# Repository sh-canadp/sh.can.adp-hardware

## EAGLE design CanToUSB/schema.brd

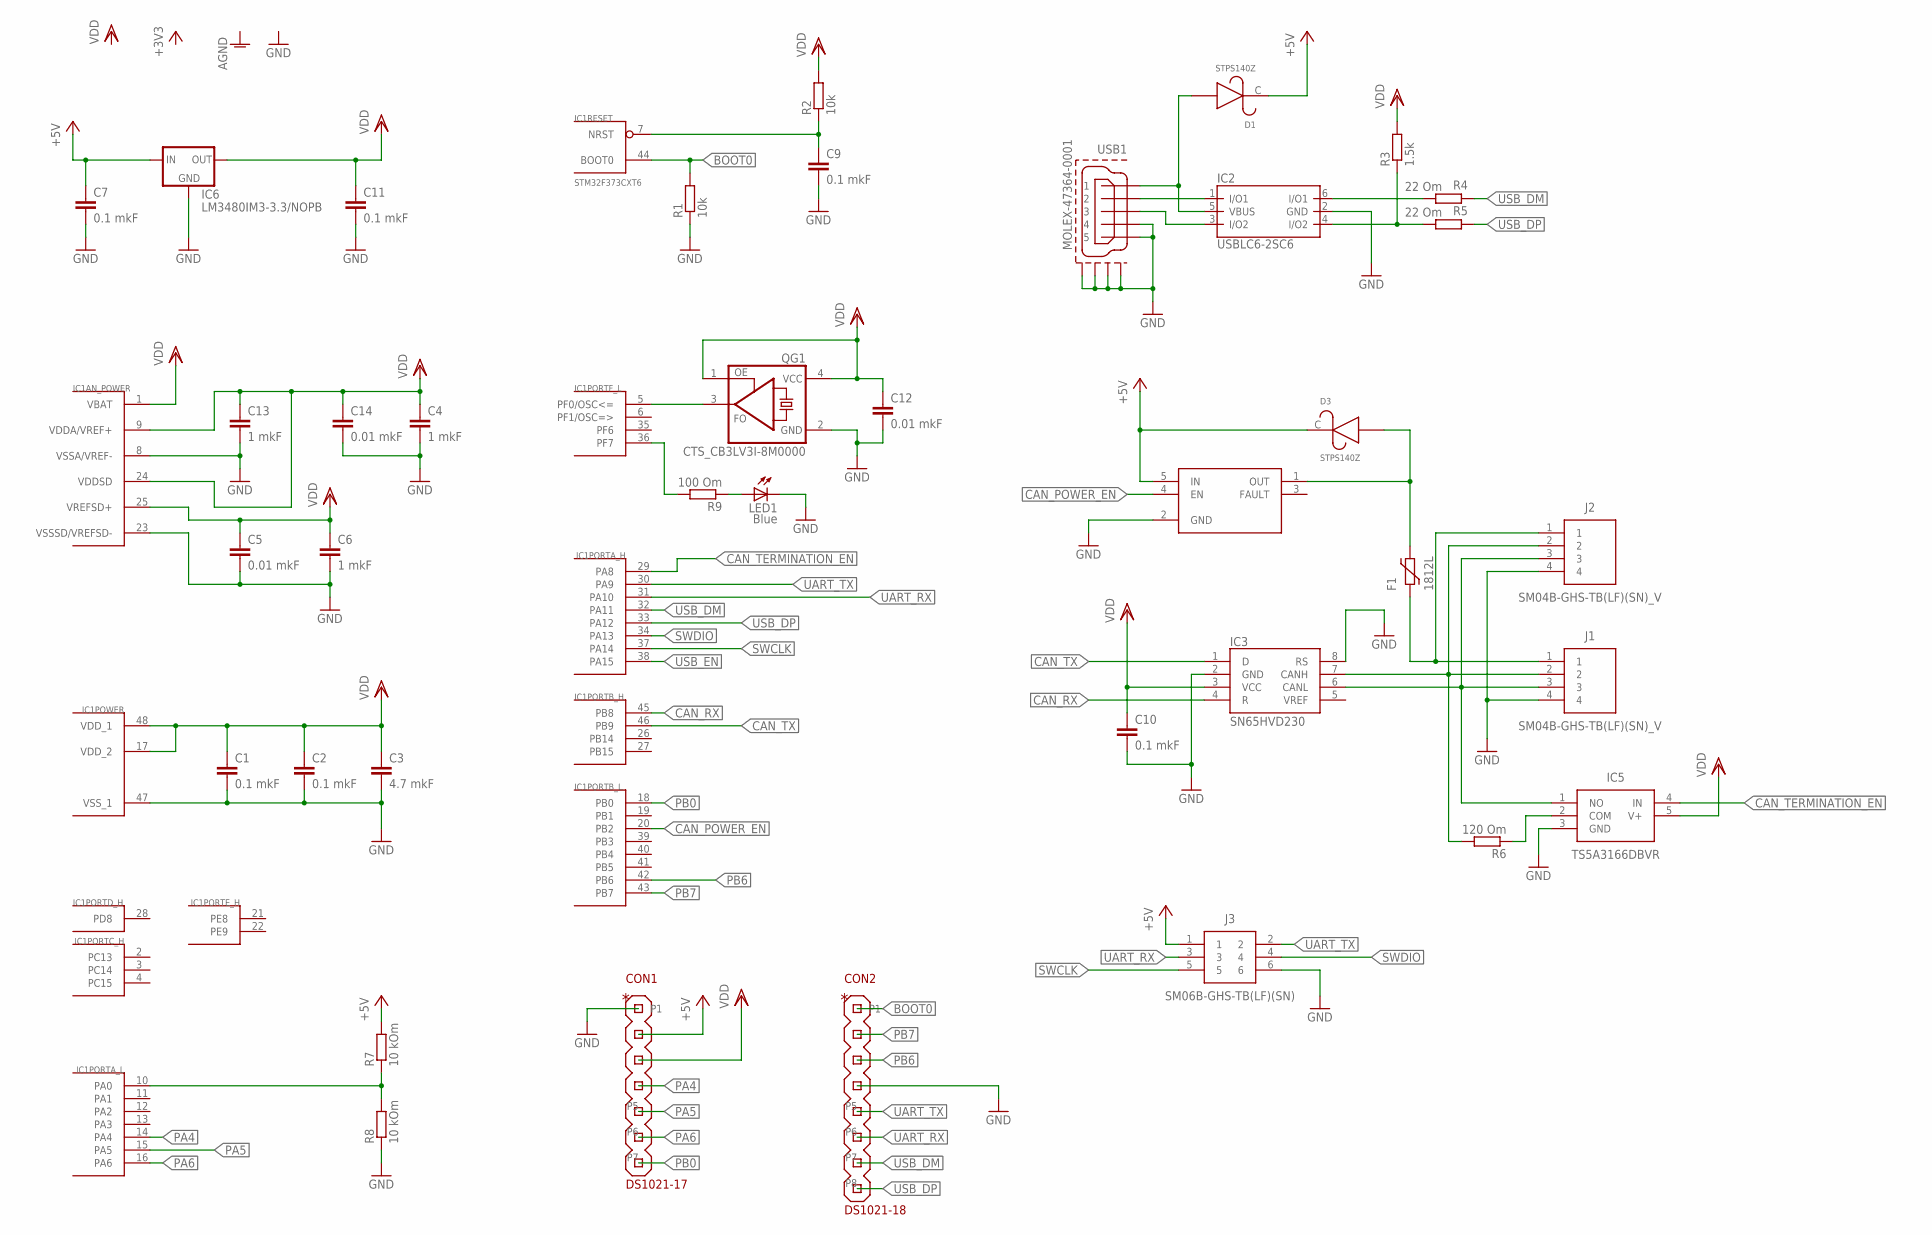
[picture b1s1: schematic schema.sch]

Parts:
C1, C2, C7, C9, C10, C11: 0.1 mkF; C0603
C3: 4.7 mkF; C0805
C4, C6, C13: 1 mkF; C0603
C5, C12, C14: 0.01 mkF; C0603
CON1: DS1021-17; DS1021-1*7
CON2: DS1021-18; DS1021-1*8
D1, D3: STPS140Z; SOD123
F1: 1812L
IC1: STM32F373CXT6; TQFP48
IC2: USBLC6-2SC6; SOT23-6L
IC3: SN65HVD230; SO8
IC5: TS5A3166DBVR; SOT23-5
IC6: LM3480IM3-3.3/NOPB; SOT23
IC7: STMPS2171STR; SOT23-5L
J1, J2: SM04B-GHS-TB(LF)(SN)_V; SM04B-GHS-TB
J3: SM06B-GHS-TB(LF)(SN); SM06B-GHS-TB
LED1: Blue; CHIPLED_0603
QG1: CTS_CB3LV3I-8M0000; CTS_CB3
R1, R2: 10k; R0603
R3: 1.5k; R0603
R4, R5: 22 Om; R0603
R6: 120 Om; R1206
R7, R8: 10 kOm; R0603
R9: 100 Om; R0603
USB1: MOLEX-47364-0001

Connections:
+5V: C7.1, CON1.P2, D1.C, D3.C, IC6.2 (IN), IC7.5 (IN), J3.1, R7.2
BOOT0: CON2.P1, IC1.44 (BOOT0), R1.2
CAN_POWER_EN: IC1.20 (PB2), IC7.4 (EN)
CAN_RX: IC1.45 (PB8), IC3.4 (R)
CAN_TERMINATION_EN: IC1.29 (PA8), IC5.4 (IN)
CAN_TX: IC1.46 (PB9), IC3.1 (D)
GND: C1.2, C2.2, C3.2, C4.2, C5.2, C6.2, C7.2, C9.2, C10.2, C11.2, C12.2, C13.2, C14.2, CON1.P1, CON2.P4, IC1.8 (VSSA/VREF-), IC1.23 (VSSSD/VREFSD-), IC1.47 (VSS_1), IC2.2 (GND), IC3.2 (GND), IC3.8 (RS), IC5.3 (GND), IC6.3 (GND), IC7.2 (GND), J1.4, J2.4, J3.6, LED1.C, QG1.2 (GND), R1.1, R8.1, USB1.4, USB1.5, USB1.GND1, USB1.GND2, USB1.GND3, USB1.GND4
unnamed: C9.1, IC1.7 (NRST), R2.1
unnamed: IC1.5 (PF0/OSC<=), QG1.3 (FO)
unnamed: IC3.7 (CANH), J1.2, J2.2, R6.2
unnamed: IC2.1 (I/O1), USB1.2
unnamed: IC2.3 (I/O2), USB1.3
unnamed: IC2.6 (I/O1), R4.2
unnamed: IC2.4 (I/O2), R3.1, R5.2
unnamed: IC3.6 (CANL), IC5.1 (NO), J1.3, J2.3
unnamed: D3.A, F1.2, IC7.1 (OUT)
unnamed: IC5.2 (COM), R6.1
unnamed: F1.1, J1.1, J2.1
unnamed: D1.A, IC2.5 (VBUS), USB1.1
unnamed: IC1.10 (PA0), R7.1, R8.2
unnamed: IC1.36 (PF7), R9.2
unnamed: LED1.A, R9.1
PA4: CON1.P4, IC1.14 (PA4)
PA5: CON1.P5, IC1.15 (PA5)
PA6: CON1.P6, IC1.16 (PA6)
PB0: CON1.P7, IC1.18 (PB0)
PB6: CON2.P3, IC1.42 (PB6)
PB7: CON2.P2, IC1.43 (PB7)
SWCLK: IC1.37 (PA14), J3.5
SWDIO: IC1.34 (PA13), J3.4
UART_RX: CON2.P6, IC1.31 (PA10), J3.3
UART_TX: CON2.P5, IC1.30 (PA9), J3.2
USB_DM: CON2.P7, IC1.32 (PA11), R4.1
USB_DP: CON2.P8, IC1.33 (PA12), R5.1
USB_EN: IC1.38 (PA15)
VDD: C1.1, C2.1, C3.1, C4.1, C5.1, C6.1, C10.1, C11.1, C12.1, C13.1, C14.1, CON1.P3, IC1.1 (VBAT), IC1.9 (VDDA/VREF+), IC1.17 (VDD_2), IC1.24 (VDDSD), IC1.25 (VREFSD+), IC1.48 (VDD_1), IC3.3 (VCC), IC5.5 (V+), IC6.1 (OUT), QG1.1 (OE), QG1.4 (VCC), R2.2, R3.2

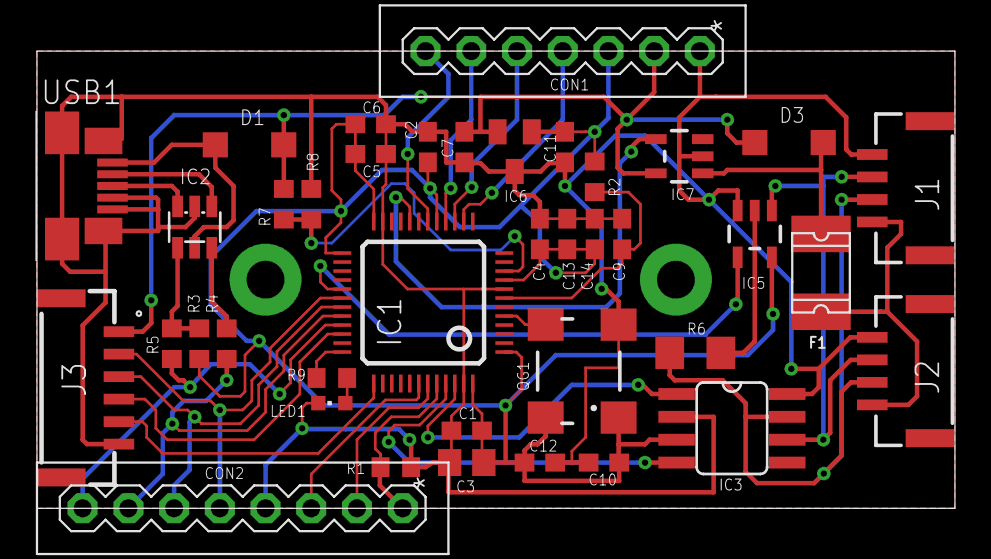
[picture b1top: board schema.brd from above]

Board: 2 copper layers, 51.0 x 25.4 mm, 39 parts (0 on the bottom side), 35 nets.

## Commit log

2018-05-08 start
